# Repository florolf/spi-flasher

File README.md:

# spi-flasher

This repository contains an USB-C-to-SPI-flash adapter that is compatible with
[stm32-vserprog](https://github.com/dword1511/stm32-vserprog/) and also has
integrated level-shifters towards the SPI flash. This was created mainly to try
out the JLCPCB assembly service and because there is no convenient way to
program 1.8V flash chips with the "Bluepill + mess of wires" setup I was using
before. The pinout is arranged such that it matches the common flash test
clips.

Furthermore, there is a simple breakout board that flash chips can be directly
soldered onto if space in the target device is too tight to use such a clip
(this is mainly useful when reverse-engineering third-party hardware).

## Hardware

The respective `fab` directories contain fabrication data (and in the case of
the adapter, JLCPCB-style assembly data) for the boards. As JLCPCB cannot
populate connectors at this time, those had to be assembled manually:

 - The dual-row 100mil connector is either a plain dual-row header or a
   shrouded/keyed one.
 - The USB-C connector is a particular family that I sourced from
   [AliExpress](https://aliexpress.com/item/32822609480.html). There doesn't
   seem to be alternative from western distributors that's similarly convenient
   to solder.

The way the target is powered can be selected through the pin header above the
USB port: The target can be self-powered (no jumper), powered from the internal
3.3V rail (jumper between 3.3 and Vt) or powered externally (supply power
between G and Vt).

The TRST/GND connector was meant as an extension that could be used (given a
modified version of `stm32-vserprog`) to keep a target device in reset while
accessing the flash to prevent interference. However, this does not really work
out mechanically, so it was never used.

## Firmware

Build `stm32-vserprog` using `BOARD=stm32-jz01v20` and flash the firmware via
the TagConnect connector.

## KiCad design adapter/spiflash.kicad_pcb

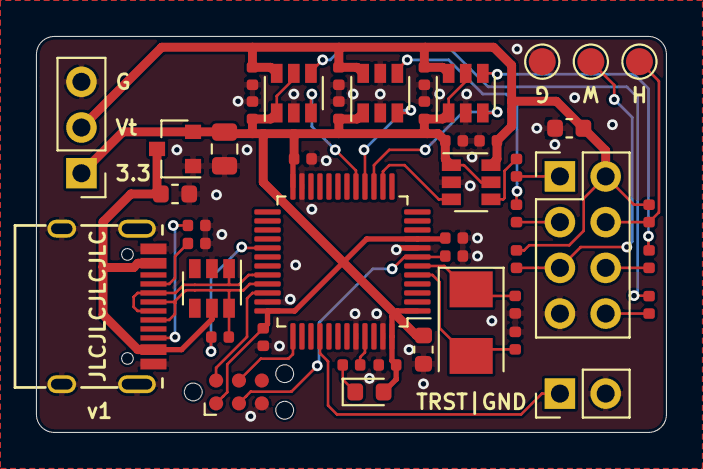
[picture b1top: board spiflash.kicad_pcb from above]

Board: 2 copper layers, 35.0 x 22.0 mm, 46 parts (0 on the bottom side), 31 nets.

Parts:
C1, C5, C7: 1u; C_0603_1608Metric
C2: 10u; C_0805_2012Metric
C3, C6: 20p; C_0402_1005Metric
C4, C8, C9, C10, C11, C12, C13, C14, C15, C16, C17, C18, C19: 100n; C_0402_1005Metric
D1: green; LED_0603_1608Metric
J1: USB_C_Receptacle_USB2.0; USB-C_16Pin
J2: Tag-Connect; Tag-Connect_TC2030-IDC-NL_2x03_P1.27mm_Vertical
J3: Conn_01x02; PinHeader_1x02_P2.54mm_Vertical
J4: Conn_01x03; PinHeader_1x03_P2.54mm_Vertical
J5: Clip; PinHeader_2x04_P2.54mm_Vertical
R1, R2: 5k1; R_0402_1005Metric
R3: 220R; R_0402_1005Metric
R4, R5, R9, R10: 33R; R_0402_1005Metric
R6: 1k5; R_0402_1005Metric
R7, R8: 1k; R_0402_1005Metric
TP1, TP2, TP3: TestPoint; TestPoint_Pad_D1.5mm
U1: XC6206; SOT-23
U2: SRV05-4-P-T7; SOT-23-6
U4: STM32F103C8T6; LQFP-48_7x7mm_P0.5mm
U5, U6, U7, U8: SN74LVC1T45DBV; SOT-23-6
Y1: 8MHz; Crystal_SMD_5032-2Pin_5.0x3.2mm

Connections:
+3V3: C2.1, C7.1, C8.1, C9.1, C10.1, C11.1, C12.1, C13.1, C16.1, C17.1, D1.2, J2.1, J4.1, U1.2, U4.1, U4.9, U4.24, U4.36, U4.48, U5.1, U5.5, U6.1, U6.5, U7.1, U7.5, U8.1
/HOLD: J5.4, R7.2, TP2.1
/MISO: R5.1, U8.4
/MISO_MCU: U4.16, U8.3
/MOSI: R10.1, U6.4
/MOSI_MCU: U4.17, U6.3
/NRST: C4.1, J2.3, U4.7
/NSS: R4.1, U5.4
/NSS_MCU: U4.14, U5.3
/SCK: R9.1, U7.4
/SCK_MCU: U4.15, U7.3
/SWCLK: J2.4, U4.37
/SWDIO: J2.2, U4.34
/TRST: J3.1, U4.40
/USB_DM: J1.A7, J1.B7, U2.1, U4.32
/USB_DP: J1.A6, J1.B6, R6.2, U2.6, U4.33
/V_TARGET: C5.1, C14.1, C15.1, C18.1, C19.1, J4.2, J5.2, R7.1, R8.1, U5.6, U6.6, U7.6, U8.6
/WP: J5.5, R8.2, TP3.1
GND: C1.2, C2.2, C3.2, C4.2, C5.2, C6.2, C7.2, C8.2, C9.2, C10.2, C11.2, C12.2, C13.2, C14.2, C15.2, C16.2, C17.2, C18.2, C19.2, J1.A1, J1.B1, J1.S1, J2.5, J3.2, J4.3, J5.7, R1.1, R2.1, TP1.1, U1.1, U2.2, U4.8, U4.23, U4.35, U4.44, U4.47, U5.2, U6.2, U7.2, U8.2, U8.5
unnamed: C3.1, U4.5, Y1.2
unnamed: C6.1, U4.6, Y1.1
unnamed: D1.1, R3.2
unnamed: J1.A5, R1.2
unnamed: J1.B5, R2.2
unnamed: J5.1, R4.2
unnamed: J5.3, R5.2
unnamed: J5.6, R9.2
unnamed: J5.8, R10.2
unnamed: R3.1, U4.45
unnamed: R6.1, U4.29
VBUS: C1.1, J1.A4, J1.B4, U1.3, U2.5

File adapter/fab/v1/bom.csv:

Comment,Designator,Footprint,LCSC, LCSC, MPN, Manufacturer, DNP
"10u","C2","Capacitor_SMD:C_0805_2012Metric","","C15850","CL21A106KAYNNNE","Samsung Electro-Mechanics",""
"20p","C3,C6","Capacitor_SMD:C_0402_1005Metric","","C1554","0402CG200J500NT","Guangdong Fenghua Advanced Tech",""
"100n","C4,C8,C9,C10,C13,C11,C14,C16,C18,C17,C19,C12,C15","Capacitor_SMD:C_0402_1005Metric","","C1525","CL05B104KO5NNNC","Samsung Electro-Mechanics",""
"1u","C7,C1,C5","Capacitor_SMD:C_0603_1608Metric","","C15849","CL10A105KB8NNNC","Samsung Electro-Mechanics",""
"green","D1","LED_SMD:LED_0603_1608Metric","","C72043","19-217/GHC-YR1S2/3T","Everlight Elec",""
"USB_C_Receptacle_USB2.0","J1","footprints:USB-C_16Pin",""
"Tag-Connect","J2","Connector:Tag-Connect_TC2030-IDC-NL_2x03_P1.27mm_Vertical","","","","","DNP"
"Conn_01x02","J3","Connector_PinHeader_2.54mm:PinHeader_1x02_P2.54mm_Vertical",""
"Conn_01x03","J4","Connector_PinHeader_2.54mm:PinHeader_1x03_P2.54mm_Vertical",""
"Clip","J5","Connector_PinHeader_2.54mm:PinHeader_2x04_P2.54mm_Vertical",""
"5k1","R1,R2","Resistor_SMD:R_0402_1005Metric","","C25905","0402WGF5101TCE","Uniroyal Elec",""
"220R","R3","Resistor_SMD:R_0402_1005Metric","","C25091","0402WGF2200TCE","Uniroyal Elec",""
"1k5","R6","Resistor_SMD:R_0402_1005Metric","","C25867","0402WGF1501TCE","Uniroyal Elec",""
"1k","R7,R8","Resistor_SMD:R_0402_1005Metric","","C11702","0402WGF1001TCE","Uniroyal Elec",""
"33R","R9,R10,R4,R5","Resistor_SMD:R_0402_1005Metric","","C25105","0402WGF330JTCE","Uniroyal Elec",""
"TestPoint","TP3,TP2,TP1","TestPoint:TestPoint_Pad_D1.5mm","","","","","DNP"
"XC6206","U1","Package_TO_SOT_SMD:SOT-23","","C5446","XC6206P332MR","Torex Semicon",""
"SRV05-4-P-T7","U2","Package_TO_SOT_SMD:SOT-23-6","","C85364","SRV05-4-P-T7","ProTek Devices",""
"STM32F103C8T6","U4","Package_QFP:LQFP-48_7x7mm_P0.5mm","","C8734","STM32F103C8T6","STMicroelectronics",""
"SN74LVC1T45DBV","U5,U7,U8,U6","Package_TO_SOT_SMD:SOT-23-6","","C7843","SN74LVC1T45DBVR","Texas Instruments",""
"8MHz","Y1","Crystal:Crystal_SMD_5032-2Pin_5.0x3.2mm","","C115962","X50328MSB2GI","Yangxing Tech",""

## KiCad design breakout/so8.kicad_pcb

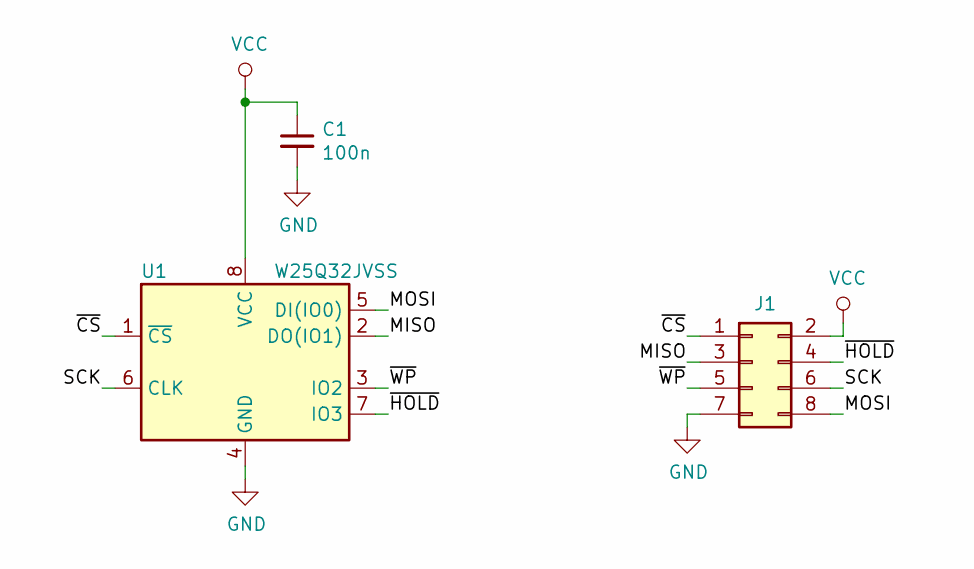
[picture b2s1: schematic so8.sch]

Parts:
C1: 100n; C_0402_1005Metric
J1: Conn_02x04_Odd_Even; PinSocket_2x04_P1.00mm_Vertical_SMD
U1: W25Q32JVSS; SOIC-8_5.23x5.23mm_P1.27mm

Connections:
/MISO: J1.3, U1.2 (DO(IO1))
/MOSI: J1.8, U1.5 (DI(IO0))
/SCK: J1.6, U1.6 (CLK)
/~CS: J1.1, U1.1 (~CS)
/~HOLD: J1.4, U1.7 (IO3)
/~WP: J1.5, U1.3 (IO2)
GND: C1.2, J1.7, U1.4 (GND)
VCC: C1.1, J1.2, U1.8 (VCC)

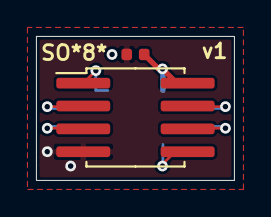
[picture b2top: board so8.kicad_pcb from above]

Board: 2 copper layers, 11.0 x 8.0 mm, 3 parts (1 on the bottom side), 8 nets.

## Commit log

2019-09-22 import
2019-09-22 move stuff
2019-09-23 adapter: make ERC happy
2019-09-23 remap TRST
2019-09-23 add so8 breakout
2019-09-23 so8: add fab files
2019-09-23 adapter: add Vtarget decoupling
2019-09-23 don't ignore CSVs
2019-09-23 adapter: generate fab data
2019-09-23 adapter: define crystal loading caps, reexport fab
2019-09-23 adapter: update CPL to JLC conventions
2019-09-23 adapter: fix CPL rotations
2019-12-17 add README
2019-12-27 breakout: add PWR_FLAGs
    Add PWR_FLAGs to the supply lines to silence ERC warnings.
    Fixes #2.
